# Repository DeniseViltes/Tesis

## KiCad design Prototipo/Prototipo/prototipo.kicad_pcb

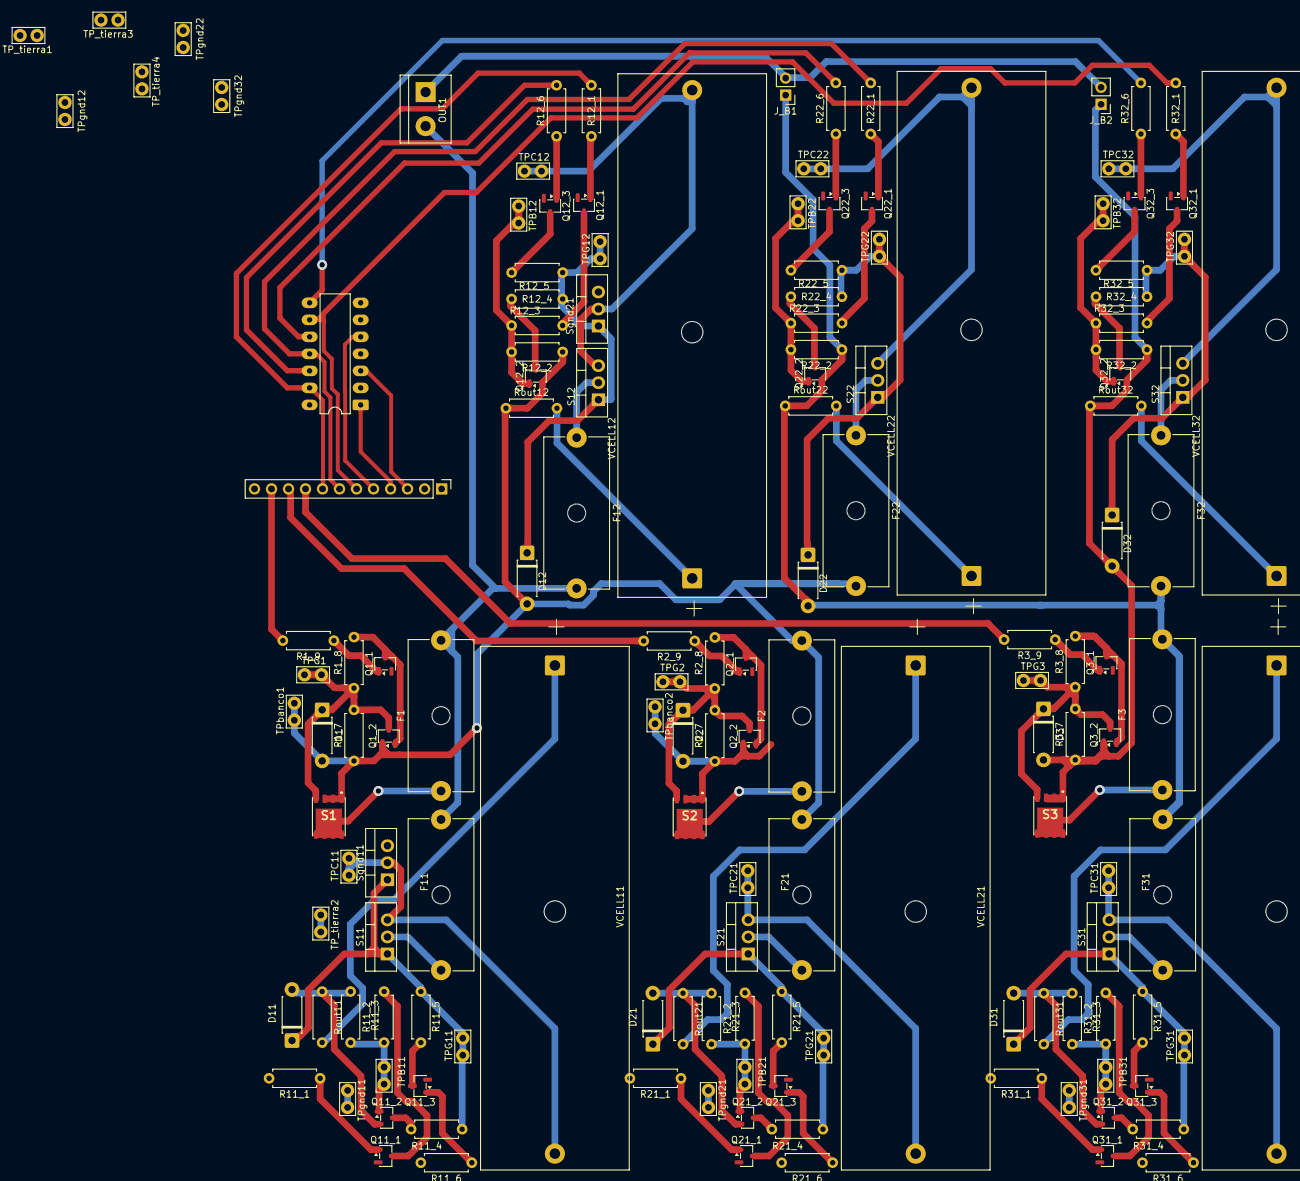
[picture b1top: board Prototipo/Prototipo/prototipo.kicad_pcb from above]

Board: 2 copper layers, 148 parts (0 on the bottom side), 94 nets.

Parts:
A1: DIP-14_W7.62mm_LongPads
D1, D2, D3, D11, D12, D21, D22, D31, D32: 1N4736A; D_DO-41_SOD81_P7.62mm_Horizontal
F1, F2, F3, F11, F12, F21, F22, F31, F32: Fuse; Fuseholder_Cylinder-5x20mm_Schurter_0031_8201_Horizontal_Op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
IN1: Conn_01x12_Pin; PinHeader_1x12_P2.54mm_Vertical
J_B1, J_B2: Conn_01x02_Pin; PinHeader_1x02_P2.54mm_Vertical
OUT1: Conn_01x02_Socket; TerminalBlock_bornier-2_P5.08mm
Q1_1, Q2_1, Q3_1, Q11_1, Q11_3, Q12_1, Q12_3, Q21_1, Q21_3, Q22_1, Q22_3, Q31_1, Q31_3, Q32_1, Q32_3: MMBT2222A; SOT-23-3
Q1_2, Q2_2, Q3_2: MMBFJ201; SOT-23-3
Q11_2, Q12_2, Q21_2, Q22_2, Q31_2, Q32_2: MMBT2907A; SOT-23-3
R1_7, R2_7, R3_7: 570K; R_Axial_DIN0207_L6.3mm_D2.5mm_P7.62mm_Horizontal
R1_8, R2_8, R3_8: 300K; R_Axial_DIN0207_L6.3mm_D2.5mm_P7.62mm_Horizontal
R1_9, R2_9, R3_9, R11_1, R11_6, R12_1, R12_6, R21_1, R21_6, R22_1, R22_6, R31_1, R31_6, R32_1, R32_6: 20k; R_Axial_DIN0207_L6.3mm_D2.5mm_P7.62mm_Horizontal
R11_2, R12_2, R21_2, R22_2, R31_2, R32_2: 10Meg; R_Axial_DIN0207_L6.3mm_D2.5mm_P7.62mm_Horizontal
R11_3, R12_3, R21_3, R22_3, R31_3, R32_3: 1Meg; R_Axial_DIN0207_L6.3mm_D2.5mm_P7.62mm_Horizontal
R11_4, R12_4, R21_4, R22_4, R31_4, R32_4: 4.7k; R_Axial_DIN0207_L6.3mm_D2.5mm_P7.62mm_Horizontal
R11_5, R12_5, R21_5, R22_5, R31_5, R32_5: 33k; R_Axial_DIN0207_L6.3mm_D2.5mm_P7.62mm_Horizontal
Rout11, Rout12, Rout21, Rout22, Rout31, Rout32: 1m; R_Axial_DIN0207_L6.3mm_D2.5mm_P7.62mm_Horizontal
S1, S2, S3: FDMS6681Z
S11, S12, S21, S22, S31, S32: IRLB8721; TO-220-3_Vertical
Sgnd11, Sgnd21: IRLB8721; TO-220-3_Vertical
TPB11, TPB12, TPB21, TPB22, TPB31, TPB32: TestPoint; TestPoint_Bridge_Pitch2.54mm_Drill1.0mm
TPC11, TPC12, TPC21, TPC22, TPC31, TPC32: TestPoint; TestPoint_Bridge_Pitch2.54mm_Drill1.0mm
TPG1, TPG2, TPG3, TPG11, TPG12, TPG21, TPG22, TPG31, TPG32: TestPoint; TestPoint_Bridge_Pitch2.54mm_Drill1.0mm
TP_tierra1, TP_tierra2, TP_tierra3, TP_tierra4: TestPoint; TestPoint_Bridge_Pitch2.54mm_Drill1.0mm
TPbanco1, TPbanco2: TestPoint; TestPoint_Bridge_Pitch2.54mm_Drill1.0mm
TPgnd11, TPgnd12, TPgnd21, TPgnd22, TPgnd31, TPgnd32: TestPoint; TestPoint_Bridge_Pitch2.54mm_Drill1.0mm
VCELL11, VCELL12, VCELL21, VCELL22, VCELL31, VCELL32: 3.3; BatteryHolder_MPD_BK-18650-PC2

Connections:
0: A1.7 (GND), IN1.1, IN1.12, Q1_1.2 (E), Q2_1.2 (E), Q3_1.2 (E), Q11_1.2 (E), Q11_3.2 (E), Q12_1.2 (E), Q12_3.2 (E), Q21_1.2 (E), Q21_3.2 (E), Q22_1.2 (E), Q22_3.2 (E), Q31_1.2 (E), Q31_3.2 (E), Q32_1.2 (E), Q32_3.2 (E), Sgnd11.3 (S), Sgnd21.3 (S), TP_tierra1.1, TP_tierra2.1, TP_tierra3.1, TP_tierra4.1, TPgnd11.1, TPgnd12.1, TPgnd21.1, TPgnd22.1, TPgnd31.1, TPgnd32.1
/celda_11/Vcontrol_neg: A1.2, R11_6.2
/celda_11/bus_neg: F1.2, F11.2, F12.2, OUT1.2
/celda_11/bus_pos: D1.2 (-), D11.2 (-), D12.2 (-), F2.2, F21.2, F22.2, Q1_2.1 (D), Q11_2.2 (E), Q12_2.2 (E), R1_7.1, R11_2.1, R12_2.1, Rout11.1, Rout12.1, S1.1 (S_1), S1.2 (S_2), S1.3 (S_3), TPbanco1.1
/celda_11/cell_neg: S11.3 (S), Sgnd11.2 (D), TPC11.1, VCELL11.2 (-)
/celda_11/gate: D11.1 (+), R11_4.2, R11_5.1, S11.1 (G), Sgnd11.1 (G), TPG11.1
/celda_12/Vcontrol_neg: A1.12, R12_6.2
/celda_12/cell_neg: S12.3 (S), Sgnd21.2 (D), TPC12.1, VCELL12.2 (-)
/celda_12/gate: D12.1 (+), R12_4.2, R12_5.1, S12.1 (G), Sgnd21.1 (G), TPG12.1
/celda_21/Vcontrol_neg: A1.4, R21_6.2
/celda_21/bus_pos: D2.2 (-), D21.2 (-), D22.2 (-), F3.2, F31.2, F32.2, J_B1.1, Q2_2.1 (D), Q21_2.2 (E), Q22_2.2 (E), R2_7.1, R21_2.1, R22_2.1, Rout21.1, Rout22.1, S2.1 (S_1), S2.2 (S_2), S2.3 (S_3), TPbanco2.1
/celda_21/cell_neg: S21.3 (S), TPC21.1, VCELL21.2 (-)
/celda_21/gate: D21.1 (+), R21_4.2, R21_5.1, S21.1 (G), TPG21.1
/celda_22/Vcontrol_neg: A1.10, R22_6.2
/celda_22/cell_neg: S22.3 (S), TPC22.1, VCELL22.2 (-)
/celda_22/gate: D22.1 (+), R22_4.2, R22_5.1, S22.1 (G), TPG22.1
/celda_31/Vcontrol_neg: A1.6, R31_6.2
/celda_31/bus_pos: D3.2 (-), D31.2 (-), D32.2 (-), J_B2.1, Q3_2.1 (D), Q31_2.2 (E), Q32_2.2 (E), R3_7.1, R31_2.1, R32_2.1, Rout31.1, Rout32.1, S3.1 (S_1), S3.2 (S_2), S3.3 (S_3)
/celda_31/cell_neg: S31.3 (S), TPC31.1, VCELL31.2 (-)
/celda_31/gate: D31.1 (+), R31_4.2, R31_5.1, S31.1 (G), TPG31.1
/celda_32/Vcontrol_neg: A1.8, R32_6.2
/celda_32/cell_neg: S32.3 (S), TPC32.1, VCELL32.2 (-)
/celda_32/gate: D32.1 (+), R32_4.2, R32_5.1, S32.1 (G), TPG32.1
unnamed: D1.1 (+), Q1_2.3 (S), R1_7.2, R1_8.1, S1.4 (G), TPG1.1
unnamed: D2.1 (+), Q2_2.3 (S), R2_7.2, R2_8.1, S2.4 (G), TPG2.1
unnamed: D3.1 (+), Q3_2.3 (S), R3_7.2, R3_8.1, S3.4 (G), TPG3.1
unnamed: J_B1.2, J_B2.2, OUT1.1
unnamed: Q1_1.1 (B), R1_9.1
unnamed: Q1_1.3 (C), Q1_2.2 (G), R1_8.2
unnamed: Q2_1.1 (B), R2_9.1
unnamed: Q2_1.3 (C), Q2_2.2 (G), R2_8.2
unnamed: Q3_1.1 (B), R3_9.1
unnamed: Q3_1.3 (C), Q3_2.2 (G), R3_8.2
unnamed: Q11_1.1 (B), R11_1.1
unnamed: Q11_1.3 (C), R11_3.2
unnamed: Q11_2.1 (B), R11_2.2, R11_3.1, TPB11.1
unnamed: Q11_2.3 (C), R11_4.1
unnamed: Q11_3.1 (B), R11_6.1
unnamed: Q11_3.3 (C), R11_5.2
unnamed: Q12_1.1 (B), R12_1.1
unnamed: Q12_1.3 (C), R12_3.2
unnamed: Q12_2.1 (B), R12_2.2, R12_3.1, TPB12.1
unnamed: Q12_2.3 (C), R12_4.1
unnamed: Q12_3.1 (B), R12_6.1
unnamed: Q12_3.3 (C), R12_5.2
unnamed: Q21_1.1 (B), R21_1.1
unnamed: Q21_1.3 (C), R21_3.2
unnamed: Q21_2.1 (B), R21_2.2, R21_3.1, TPB21.1
unnamed: Q21_2.3 (C), R21_4.1
unnamed: Q21_3.1 (B), R21_6.1
unnamed: Q21_3.3 (C), R21_5.2
unnamed: Q22_1.1 (B), R22_1.1
unnamed: Q22_1.3 (C), R22_3.2
unnamed: Q22_2.1 (B), R22_2.2, R22_3.1, TPB22.1
unnamed: Q22_2.3 (C), R22_4.1
unnamed: Q22_3.1 (B), R22_6.1
unnamed: Q22_3.3 (C), R22_5.2
unnamed: Q31_1.1 (B), R31_1.1
unnamed: Q31_1.3 (C), R31_3.2
unnamed: Q31_2.1 (B), R31_2.2, R31_3.1, TPB31.1
unnamed: Q31_2.3 (C), R31_4.1
unnamed: Q31_3.1 (B), R31_6.1
unnamed: Q31_3.3 (C), R31_5.2
unnamed: Q32_1.1 (B), R32_1.1
unnamed: Q32_1.3 (C), R32_3.2
unnamed: Q32_2.1 (B), R32_2.2, R32_3.1, TPB32.1
unnamed: Q32_2.3 (C), R32_4.1
unnamed: Q32_3.1 (B), R32_6.1
unnamed: Q32_3.3 (C), R32_5.2
unnamed: F1.1, S1.5 (D_1), S1.6 (D_2), S1.7 (D_3), S1.8 (D_4), S1.9 (D_5)
unnamed: F2.1, S2.5 (D_1), S2.6 (D_2), S2.7 (D_3), S2.8 (D_4), S2.9 (D_5)
unnamed: F3.1, S3.5 (D_1), S3.6 (D_2), S3.7 (D_3), S3.8 (D_4), S3.9 (D_5)
unnamed: F11.1, S11.2 (D)
unnamed: F12.1, S12.2 (D)
unnamed: F21.1, S21.2 (D)
unnamed: F22.1, S22.2 (D)
unnamed: F31.1, S31.2 (D)
unnamed: F32.1, S32.2 (D)
unnamed: Rout11.2, VCELL11.1 (+)
unnamed: Rout12.2, VCELL12.1 (+)
unnamed: Rout21.2, VCELL21.1 (+)
unnamed: Rout22.2, VCELL22.1 (+)
unnamed: Rout31.2, VCELL31.1 (+)
unnamed: Rout32.2, VCELL32.1 (+)
VCC: A1.14 (VCC), IN1.2
Vc1: IN1.11, R1_9.2
Vc2: IN1.10, R2_9.2
Vc3: IN1.9, R3_9.2
Vc_11: A1.1, IN1.4, R11_1.2
Vc_12: A1.13, IN1.8, R12_1.2
Vc_21: A1.3, IN1.3, R21_1.2
Vc_22: A1.11, IN1.7, R22_1.2
Vc_31: A1.5, IN1.5, R31_1.2
Vc_32: A1.9, IN1.6, R32_1.2

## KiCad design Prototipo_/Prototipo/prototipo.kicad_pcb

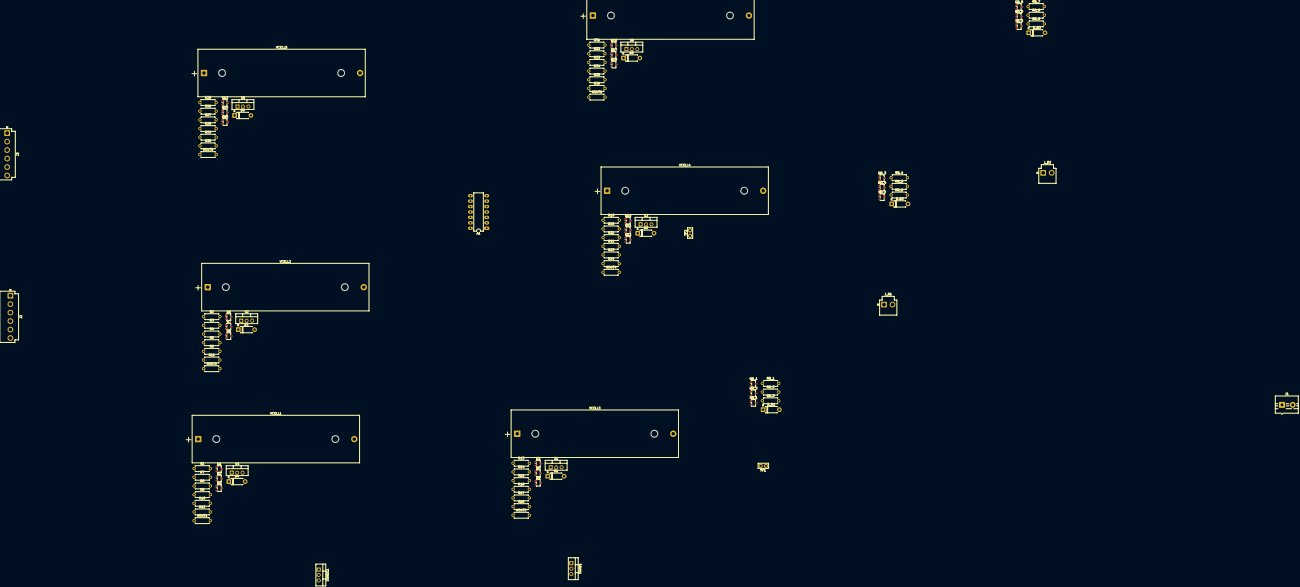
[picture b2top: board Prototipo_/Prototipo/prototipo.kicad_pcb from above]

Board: 2 copper layers, 109 parts (0 on the bottom side), 86 nets, no tracks yet.

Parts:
A1: DIP-14_W7.62mm_LongPads
D1, D2, D3, D4, D5, D6: 1N4736A; D_DO-41_SOD81_P7.62mm_Horizontal
D_B1, D_B2, D_B3: 1N4736A; D_DO-41_SOD81_P7.62mm_Horizontal
J1: Conn_01x02_Socket; TerminalBlock_MaiXu_MX126-5.0-02P_1x02_P5.00mm
J2, J3: Conn_01x06_Pin; JST_VH_B6P-VH-B_1x06_P3.96mm_Vertical
J_B1, J_B2: Conn_01x02_Pin; JST_VH_B2P-VH_1x02_P3.96mm_Vertical
Q1, Q2, Q4, Q6, Q8, Q9, Q10, Q12, Q13, Q15, Q16, Q18: MMBT2222A; SOT-23-3
Q3, Q5, Q7, Q11, Q14, Q17: MMBT2907A; SOT-23-3
QB_1, QB_3, QB_5: MMBT2222A; SOT-23-3
QB_2, QB_4, QB_6: MMBFJ201; SOT-23-3
R1, R6, R17, R23, R29, R35: 4.7k; R_Axial_DIN0207_L6.3mm_D2.5mm_P7.62mm_Horizontal
R2, R5, R7, R10, R13, R16, R19, R22, R25, R28, R31, R34: 20k; R_Axial_DIN0207_L6.3mm_D2.5mm_P7.62mm_Horizontal
R3, R8, R14, R20, R26, R32: 10Meg; R_Axial_DIN0207_L6.3mm_D2.5mm_P7.62mm_Horizontal
R4, R9, R15, R21, R27, R33: 1Meg; R_Axial_DIN0207_L6.3mm_D2.5mm_P7.62mm_Horizontal
R11, R12, R18, R24, R30, R36: 33k; R_Axial_DIN0207_L6.3mm_D2.5mm_P7.62mm_Horizontal
RB_1, RB_4, RB_7: 20k; R_Axial_DIN0207_L6.3mm_D2.5mm_P7.62mm_Horizontal
RB_2, RB_5, RB_8: 570K; R_Axial_DIN0207_L6.3mm_D2.5mm_P7.62mm_Horizontal
RB_3, RB_6, RB_9: 300K; R_Axial_DIN0207_L6.3mm_D2.5mm_P7.62mm_Horizontal
ROUT1, ROUT2, ROUT3, ROUT4, ROUT5, ROUT6: 1m; R_Axial_DIN0207_L6.3mm_D2.5mm_P7.62mm_Horizontal
S1, S2, S3, S4, S5, S6: IRLB8721; TO-220-3_Vertical
SB_1, SB_2, SB_3: AO3401A; SOT-23-3
SGND1, SGND11: IRLB8721; TO-220-3_Vertical
TP1, TP2: TestPoint; TestPoint_Bridge_Pitch2.54mm_Drill1.0mm
VCELL1, VCELL2, VCELL3, VCELL4, VCELL5, VCELL6: 3.3; BatteryHolder_MPD_BK-18650-PC2

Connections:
0: Q1.2 (E), Q2.2 (E), Q4.2 (E), Q6.2 (E), Q8.2 (E), Q9.2 (E), Q10.2 (E), Q12.2 (E), Q13.2 (E), Q15.2 (E), Q16.2 (E), Q18.2 (E), QB_1.2 (E), QB_3.2 (E), QB_5.2 (E), SGND1.3 (S), SGND11.3 (S)
/celda_1/Vcontrol_neg: A1.12, R10.2
/celda_1/bus_neg: J1.2, S1.2 (D), S4.2 (D), SB_1.3 (D)
/celda_1/bus_pos: D1.2 (-), D4.2 (-), D_B1.2 (-), Q3.2 (E), Q5.2 (E), QB_2.1 (D), R8.1, R14.1, RB_2.1, ROUT1.1, ROUT3.1, S2.2 (D), S3.2 (D), SB_1.2 (S), SB_2.3 (D), TP1.1
/celda_1/cell_neg: S4.3 (S), SGND11.2 (D), VCELL1.2 (-)
/celda_1/gate: D4.1 (+), R1.2, R12.1, S4.1 (G), SGND11.1 (G)
/celda_2/Vcontrol_neg: A1.2, R16.2
/celda_2/cell_neg: S1.3 (S), SGND1.2 (D), VCELL3.2 (-)
/celda_2/gate: D1.1 (+), R17.2, R18.1, S1.1 (G), SGND1.1 (G)
/celda_3/Vcontrol_neg: A1.10, R5.2
/celda_3/bus_pos: D2.2 (-), D3.2 (-), D_B2.2 (-), J_B1.1, Q7.2 (E), Q11.2 (E), QB_4.1 (D), R3.1, R20.1, RB_5.1, ROUT2.1, ROUT4.1, S5.2 (D), S6.2 (D), SB_2.2 (S), SB_3.3 (D), TP2.1
/celda_3/cell_neg: S2.3 (S), VCELL2.2 (-)
/celda_3/gate: D2.1 (+), R6.2, R11.1, S2.1 (G)
/celda_4/Vcontrol_neg: A1.4, R22.2
/celda_4/cell_neg: S3.3 (S), VCELL4.2 (-)
/celda_4/gate: D3.1 (+), R23.2, R24.1, S3.1 (G)
/celda_5/Vcontrol_neg: A1.8, R28.2
/celda_5/bus_pos: D5.2 (-), D6.2 (-), D_B3.2 (-), J_B2.1, Q14.2 (E), Q17.2 (E), QB_6.1 (D), R26.1, R32.1, RB_8.1, ROUT5.1, ROUT6.1, SB_3.2 (S)
/celda_5/cell_neg: S5.3 (S), VCELL5.2 (-)
/celda_5/gate: D5.1 (+), R29.2, R30.1, S5.1 (G)
/celda_6/Vcontrol_neg: A1.6, R34.2
/celda_6/cell_neg: S6.3 (S), VCELL6.2 (-)
/celda_6/gate: D6.1 (+), R35.2, R36.1, S6.1 (G)
GND: A1.7 (GND), J2.1
unnamed: D_B1.1 (+), QB_2.3 (S), RB_2.2, RB_3.1, SB_1.1 (G)
unnamed: D_B2.1 (+), QB_4.3 (S), RB_5.2, RB_6.1, SB_2.1 (G)
unnamed: D_B3.1 (+), QB_6.3 (S), RB_8.2, RB_9.1, SB_3.1 (G)
unnamed: J1.1, J_B1.2, J_B2.2
unnamed: Q1.1 (B), R7.1
unnamed: Q1.3 (C), R9.2
unnamed: Q2.1 (B), R13.1
unnamed: Q2.3 (C), R15.2
unnamed: Q3.1 (B), R8.2, R9.1
unnamed: Q3.3 (C), R1.1
unnamed: Q4.1 (B), R10.1
unnamed: Q4.3 (C), R12.2
unnamed: Q5.1 (B), R14.2, R15.1
unnamed: Q5.3 (C), R17.1
unnamed: Q6.1 (B), R2.1
unnamed: Q6.3 (C), R4.2
unnamed: Q7.1 (B), R3.2, R4.1
unnamed: Q7.3 (C), R6.1
unnamed: Q8.1 (B), R5.1
unnamed: Q8.3 (C), R11.2
unnamed: Q9.1 (B), R16.1
unnamed: Q9.3 (C), R18.2
unnamed: Q10.1 (B), R19.1
unnamed: Q10.3 (C), R21.2
unnamed: Q11.1 (B), R20.2, R21.1
unnamed: Q11.3 (C), R23.1
unnamed: Q12.1 (B), R22.1
unnamed: Q12.3 (C), R24.2
unnamed: Q13.1 (B), R25.1
unnamed: Q13.3 (C), R27.2
unnamed: Q14.1 (B), R26.2, R27.1
unnamed: Q14.3 (C), R29.1
unnamed: Q15.1 (B), R28.1
unnamed: Q15.3 (C), R30.2
unnamed: Q16.1 (B), R31.1
unnamed: Q16.3 (C), R33.2
unnamed: Q17.1 (B), R32.2, R33.1
unnamed: Q17.3 (C), R35.1
unnamed: Q18.1 (B), R34.1
unnamed: Q18.3 (C), R36.2
unnamed: QB_1.1 (B), RB_1.1
unnamed: QB_1.3 (C), QB_2.2 (G), RB_3.2
unnamed: QB_3.1 (B), RB_4.1
unnamed: QB_3.3 (C), QB_4.2 (G), RB_6.2
unnamed: QB_5.1 (B), RB_7.1
unnamed: QB_5.3 (C), QB_6.2 (G), RB_9.2
unnamed: ROUT1.2, VCELL1.1 (+)
unnamed: ROUT2.2, VCELL2.1 (+)
unnamed: ROUT3.2, VCELL3.1 (+)
unnamed: ROUT4.2, VCELL4.1 (+)
unnamed: ROUT5.2, VCELL5.1 (+)
unnamed: ROUT6.2, VCELL6.1 (+)
VCC: A1.14 (VCC), J2.2
Vc1: J2.5, RB_1.2
Vc2: J3.3, RB_4.2
Vc3: J3.6, RB_7.2
Vc_11: A1.13, J2.3, R7.2
Vc_12: A1.1, J2.4, R13.2
Vc_21: A1.11, R2.2
Vc_22: A1.3, R19.2
Vc_31: A1.9, R25.2
Vc_32: A1.5, R31.2

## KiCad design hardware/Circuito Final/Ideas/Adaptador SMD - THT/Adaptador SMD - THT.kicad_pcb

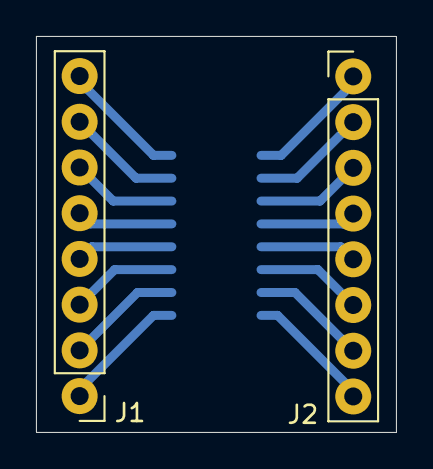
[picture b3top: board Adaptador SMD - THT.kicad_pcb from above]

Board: 2 copper layers, 20.0 x 22.0 mm, 3 parts (1 on the bottom side), 16 nets.

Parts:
J1, J2: Conn_01x08_Pin; PinHeader_1x08_P2.54mm_Vertical
U1: 74HC595; SOIC-16_3.9x9.9mm_P1.27mm

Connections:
unnamed: J1.1, U1.9 (QH')
unnamed: J1.2, U1.10 (~SRCLR)
unnamed: J1.3, U1.11 (SRCLK)
unnamed: J1.4, U1.12 (RCLK)
unnamed: J1.5, U1.13 (~OE)
unnamed: J1.6, U1.14 (SER)
unnamed: J1.7, U1.15 (QA)
unnamed: J1.8, U1.16 (VCC)
unnamed: J2.1, U1.1 (QB)
unnamed: J2.2, U1.2 (QC)
unnamed: J2.3, U1.3 (QD)
unnamed: J2.4, U1.4 (QE)
unnamed: J2.5, U1.5 (QF)
unnamed: J2.6, U1.6 (QG)
unnamed: J2.7, U1.7 (QH)
unnamed: J2.8, U1.8 (GND)

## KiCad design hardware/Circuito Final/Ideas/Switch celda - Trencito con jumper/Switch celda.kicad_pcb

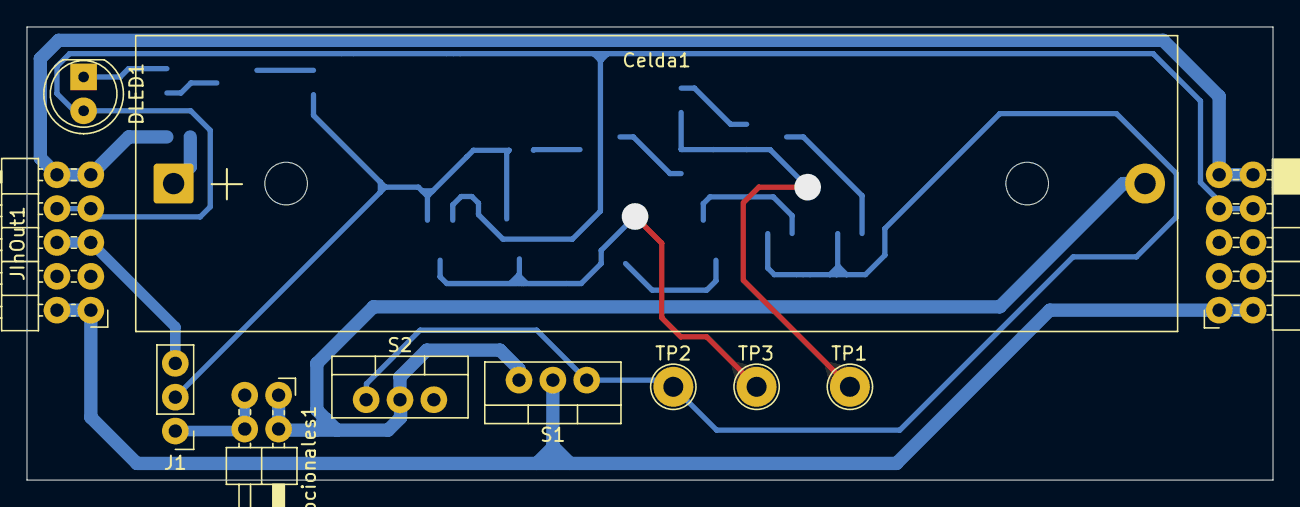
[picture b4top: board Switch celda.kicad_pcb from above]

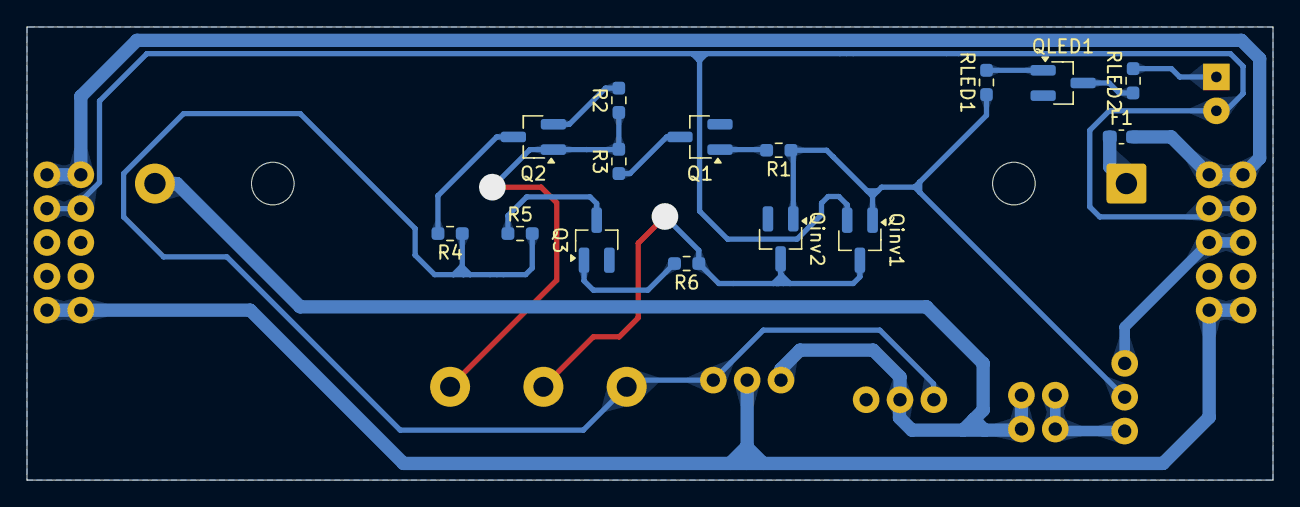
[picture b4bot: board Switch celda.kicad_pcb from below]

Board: 2 copper layers, 93.5 x 34.0 mm, 26 parts (15 on the bottom side), 20 nets.

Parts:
Celda1: Portapilas 18650; BatteryHolder_MPD_BK-18650-PC2
DLED1: LED; LED_D5.0mm
F1: Fuse_0603_1608Metric_Pad1.05x0.95mm_HandSolder
J1: Conn_01x03_Pin; PinHeader_1x03_P2.54mm_Vertical
JInOut1: Conn_02x05_Odd_Even; PinHeader_2x05_P2.54mm_Horizontal
JInOut2: Conn_02x05_Odd_Even; PinSocket_2x05_P2.54mm_Horizontal
Jopcionales1: Conn_02x02_Odd_Even; PinHeader_2x02_P2.54mm_Horizontal
Q1, Q3: MMBT2222A; SOT-23_Handsoldering
Q2: MMBT2907A; SOT-23_Handsoldering
QLED1: MMBT2222A; SOT-23_Handsoldering
Qinv1: AO3401; SOT-23_Handsoldering
Qinv2: AO3400; SOT-23_Handsoldering
R1, R6: 20k; R_0603_1608Metric_Pad0.98x0.95mm_HandSolder
R2, R3: TBD; R_0603_1608Metric_Pad0.98x0.95mm_HandSolder
R4: 4.7k; R_0603_1608Metric_Pad0.98x0.95mm_HandSolder
R5: 33k; R_0603_1608Metric_Pad0.98x0.95mm_HandSolder
RLED1: 20k; R_0603_1608Metric_Pad0.98x0.95mm_HandSolder
RLED2: 1k; R_0603_1608Metric_Pad0.98x0.95mm_HandSolder
S1, S2: IRLB8721; TO-220-3_Vertical
TP1: TP_base; TestPoint_Loop_D2.54mm_Drill1.5mm_Beaded
TP2: TP_gate; TestPoint_Loop_D2.54mm_Drill1.5mm_Beaded
TP3: TP_inv; TestPoint_Loop_D2.54mm_Drill1.5mm_Beaded

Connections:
0: JInOut1.3, JInOut1.4, JInOut2.3, JInOut2.4, Q1.3 (E), Q3.3 (E), QLED1.3 (E), Qinv2.3 (S), S2.3 (S)
unnamed: Celda1.1 (+), F1.1
unnamed: DLED1.1 (K), RLED2.2
unnamed: Q1.2 (B), R1.2
unnamed: Q1.1 (C), R3.1
unnamed: Q2.2 (B), R2.1, R3.2, TP1.1
unnamed: Q2.1 (C), R4.2
unnamed: Q3.2 (B), R6.2
unnamed: Q3.1 (C), R5.1
unnamed: QLED1.2 (B), RLED1.2
unnamed: QLED1.1 (C), RLED2.1
unnamed: Qinv1.1 (D), Qinv2.1 (D), R6.1, TP3.1
unnamed: R4.1, R5.2, S1.2 (G), S2.2 (G), TP2.1
Vcc: DLED1.2 (A), JInOut1.7, JInOut1.8, JInOut2.7, JInOut2.8, Qinv1.3 (S)
Vcell: J1.1, Jopcionales1.3, Jopcionales1.4
Vcell_banco: J1.3, JInOut1.5, JInOut1.6, JInOut2.5, JInOut2.6
Vin: J1.2, Qinv1.2 (G), Qinv2.2 (G), R1.1, RLED1.1
bus_neg: JInOut1.1, JInOut1.2, JInOut2.1, JInOut2.2, S1.1 (D)
bus_pos: F1.2, JInOut1.9, JInOut1.10, JInOut2.9, JInOut2.10, Q2.3 (E), R2.2
cell_neg: Celda1.2 (-), Jopcionales1.1, Jopcionales1.2, S1.3 (S), S2.1 (D)
